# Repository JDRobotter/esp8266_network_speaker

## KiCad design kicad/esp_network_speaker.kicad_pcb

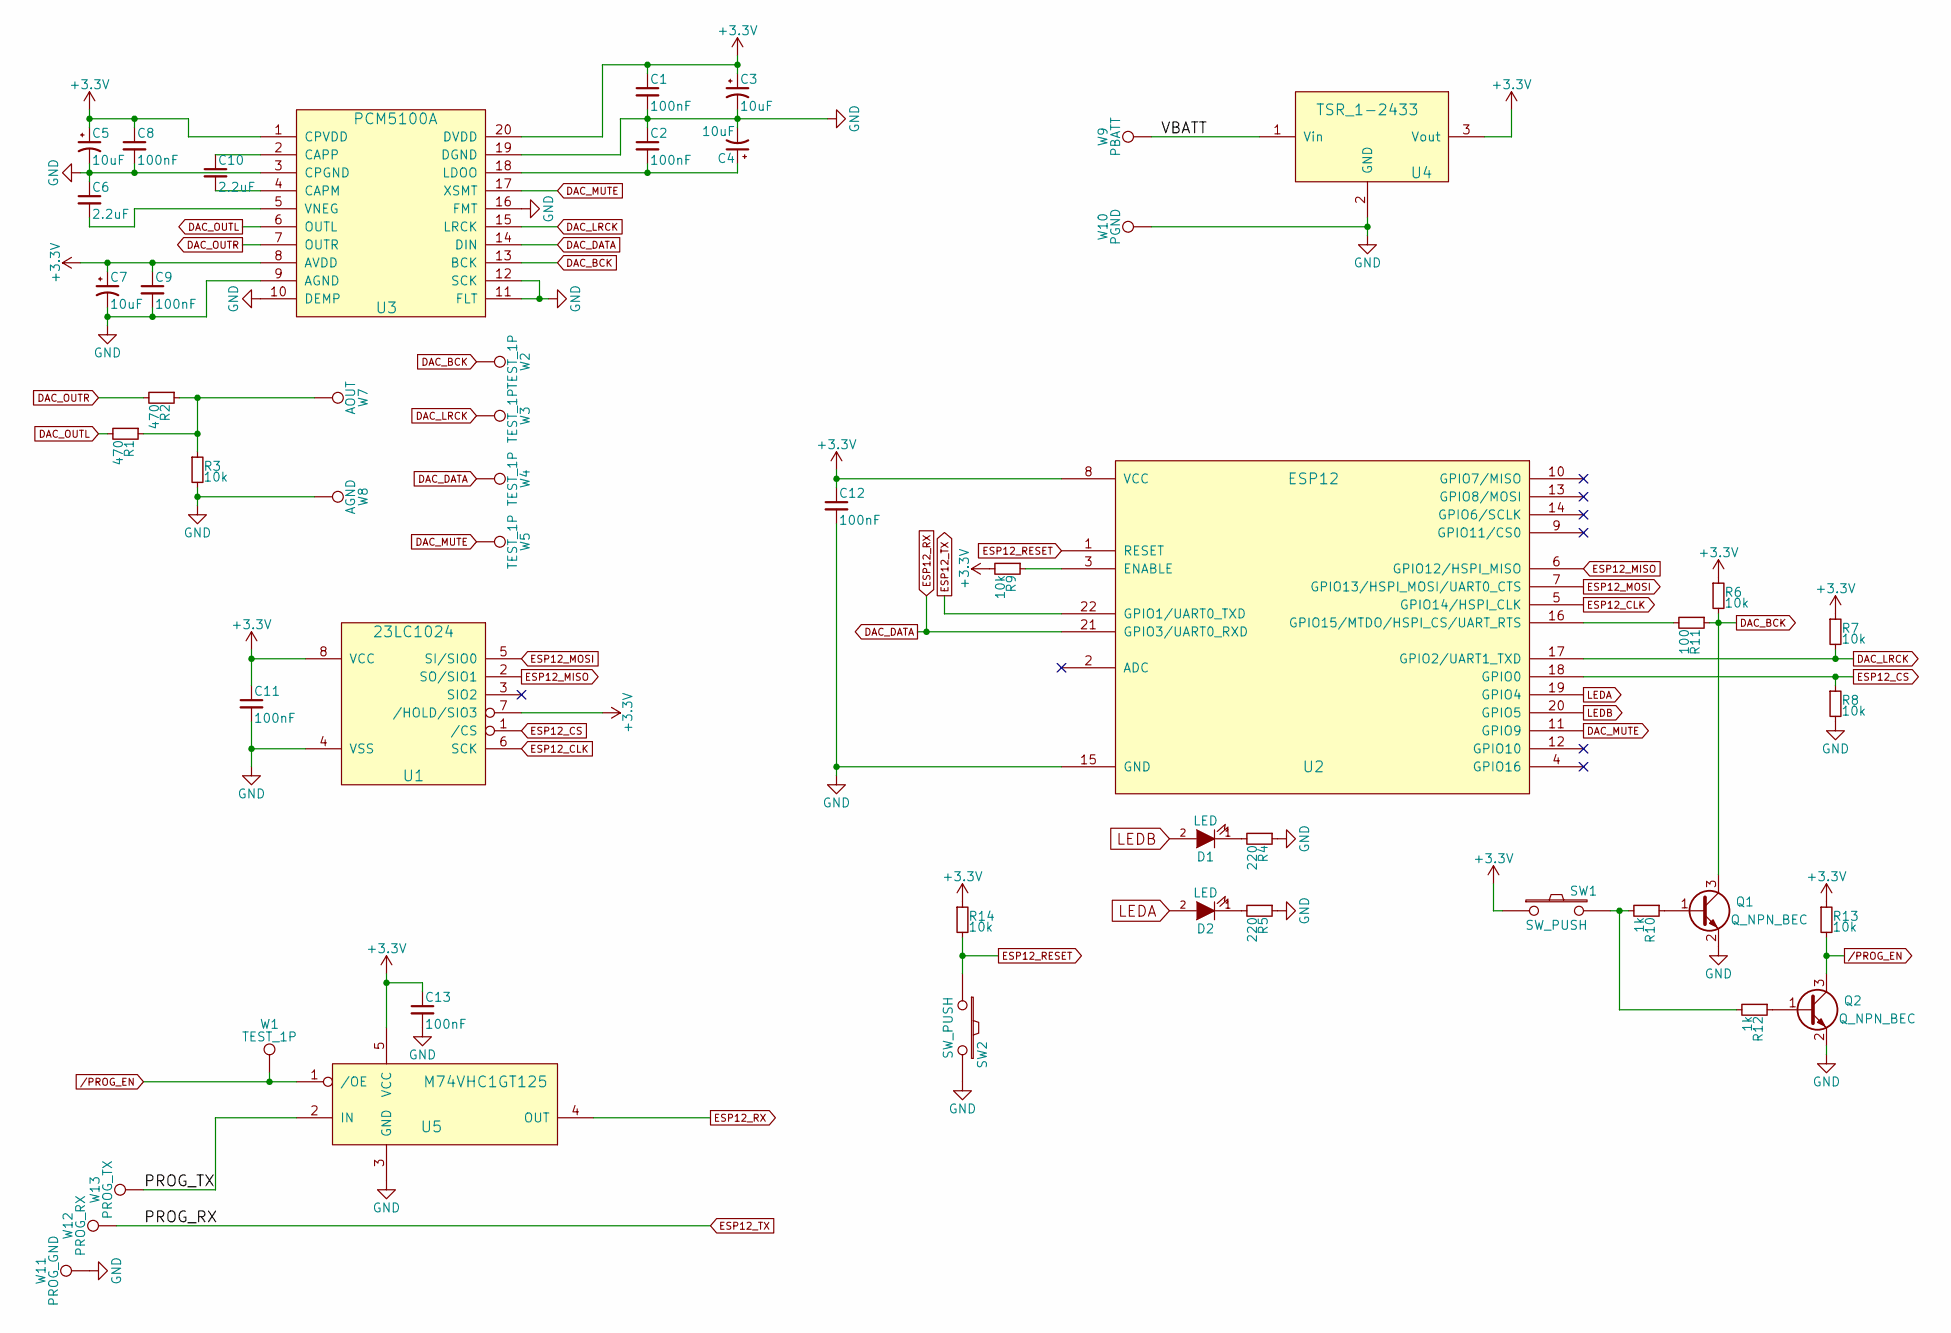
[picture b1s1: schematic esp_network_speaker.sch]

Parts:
C1, C2, C8, C9, C11, C12, C13: 100nF; C_0603_HandSoldering
C3, C4, C5, C7: 10uF; C_0603_HandSoldering
C6, C10: 2.2uF; C_0603_HandSoldering
D1, D2: LED; R_0603_HandSoldering
Q1, Q2: Q_NPN_BEC; SOT-23
R1, R2: 470; R_0603_HandSoldering
R3, R6, R7, R8, R9, R13, R14: 10k; R_0603_HandSoldering
R4, R5: 220; R_0603_HandSoldering
R10, R12: 1k; R_0603_HandSoldering
R11: 100; R_0603_HandSoldering
SW1, SW2: SW_PUSH; SW_SPST_FSMSM
U1: 23LC1024; SOIC-8_3.9x4.9mm_Pitch1.27mm
U2: ESP12
U3: PCM5100A; TSSOP-20_4.4x6.5mm_Pitch0.65mm
U4: TSR_1-2433; TSR-1
U5: M74VHC1GT125; SOT-353
W1, W2, W3, W4, W5: TEST_1P; Measurement_Point_Round-SMD-Pad_Small
W7: AOUT; Measurement_Point_Round-SMD-Pad_Big
W8: AGND; Measurement_Point_Round-SMD-Pad_Big
W9: PBATT; Measurement_Point_Round-SMD-Pad_Big
W10: PGND; Measurement_Point_Round-SMD-Pad_Big
W11: PROG_GND; Measurement_Point_Round-SMD-Pad_Big
W12: PROG_RX; Measurement_Point_Round-SMD-Pad_Big
W13: PROG_TX; Measurement_Point_Round-SMD-Pad_Big

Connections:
+3V3: C1.1, C3.1, C5.1, C7.1, C8.1, C9.1, C11.1, C12.1, C13.1, R6.1, R7.1, R9.2, R13.1, R14.1, SW1.1, U1.7 (/HOLD/SIO3), U1.8 (VCC), U2.8 (VCC), U3.1 (CPVDD), U3.8 (AVDD), U3.20 (DVDD), U4.3 (Vout), U5.5 (VCC)
/PROG_EN: Q2.3 (C), R13.2, U5.1 (/OE), W1.1
/PROG_TX: U5.2 (IN), W13.1
/VBATT: U4.1 (Vin), W9.1
DAC_BCK: Q1.3 (C), R6.2, R11.1, U3.13 (BCK), W2.1
DAC_DATA: U2.21 (GPIO3/UART0_RXD), U3.14 (DIN), U5.4 (OUT), W4.1
DAC_LRCK: R7.2, U2.17 (GPIO2/UART1_TXD), U3.15 (LRCK), W3.1
DAC_MUTE: U2.11 (GPIO9), U3.17 (XSMT), W5.1
DAC_OUTL: R1.2, U3.6 (OUTL)
DAC_OUTR: R2.2, U3.7 (OUTR)
ESP12_CLK: U1.6 (SCK), U2.5 (GPIO14/HSPI_CLK)
ESP12_CS: R8.1, U1.1 (/CS), U2.18 (GPIO0)
ESP12_MISO: U1.2 (SO/SIO1), U2.6 (GPIO12/HSPI_MISO)
ESP12_MOSI: U1.5 (SI/SIO0), U2.7 (GPIO13/HSPI_MOSI/UART0_CTS)
ESP12_RESET: R14.2, SW2.1, U2.1 (RESET)
ESP12_TX: U2.22 (GPIO1/UART0_TXD), W12.1
GND: C1.2, C2.1, C3.2, C4.2, C5.2, C6.1, C7.2, C8.2, C9.2, C11.2, C12.2, C13.2, Q1.2 (E), Q2.2 (E), R3.2, R4.1, R5.1, R8.2, SW2.2, U1.4 (VSS), U2.15 (GND), U3.3 (CPGND), U3.9 (AGND), U3.10 (DEMP), U3.11 (FLT), U3.12 (SCK), U3.16 (FMT), U3.19 (DGND), U4.2 (GND), U5.3 (GND), W8.1, W10.1, W11.1
LEDA: D2.2 (A), U2.19 (GPIO4)
LEDB: D1.2 (A), U2.20 (GPIO5)
unnamed: C2.2, C4.1, U3.18 (LDOO)
unnamed: C6.2, U3.5 (VNEG)
unnamed: C10.1, U3.2 (CAPP)
unnamed: C10.2, U3.4 (CAPM)
unnamed: D1.1 (K), R4.2
unnamed: D2.1 (K), R5.2
unnamed: Q1.1 (B), R10.1
unnamed: Q2.1 (B), R12.1
unnamed: R1.1, R2.1, R3.1, W7.1
unnamed: R9.1, U2.3 (ENABLE)
unnamed: R10.2, R12.2, SW1.2
unnamed: R11.2, U2.16 (GPIO15/MTDO/HSPI_CS/UART_RTS)

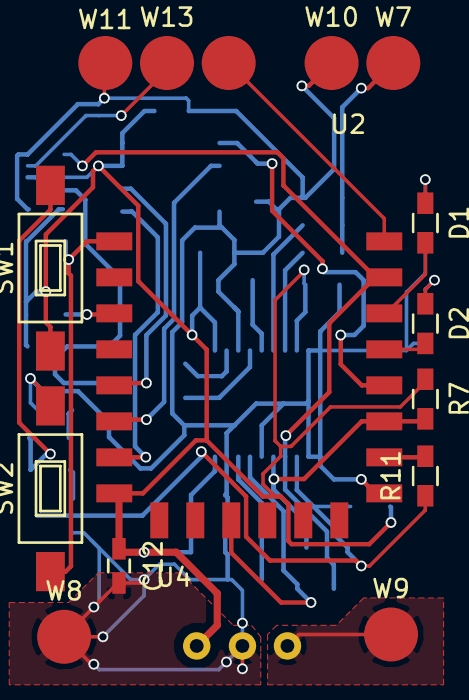
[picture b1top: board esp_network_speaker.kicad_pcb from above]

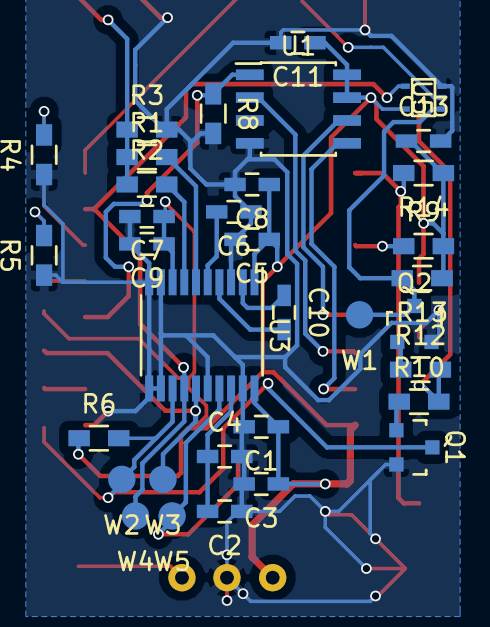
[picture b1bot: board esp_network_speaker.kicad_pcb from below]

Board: 2 copper layers, 50 parts (34 on the bottom side), 31 nets.

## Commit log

2016-10-10 init
2016-10-10 void schs and boards added
2016-10-11 wip, nothing interesting to report
2016-10-16 routing on Kicad
2016-10-20 kicad project updated
2016-11-01 wip, most of the components are in now
2016-11-01 schematic finished, some placement done
2016-11-06 routing in progress, first pass almost finished
2016-11-08 wip, gerber files generated for rev A
